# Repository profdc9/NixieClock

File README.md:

This a Nixie clock that uses IN-14 tubes and very generic, cheap, available through-hole parts so that it may be easily sourced in the future.  This material is copyrighted by Daniel Marks (KW4TI) and licensed under the Creative Commons License CC-BY-SA 4.0.  The software is licensed under the zlib license.  These are open source licenses that permit commercial use, modification and redistribution with attribution, and require licensees to assume all risk for using the copyrighted materials.

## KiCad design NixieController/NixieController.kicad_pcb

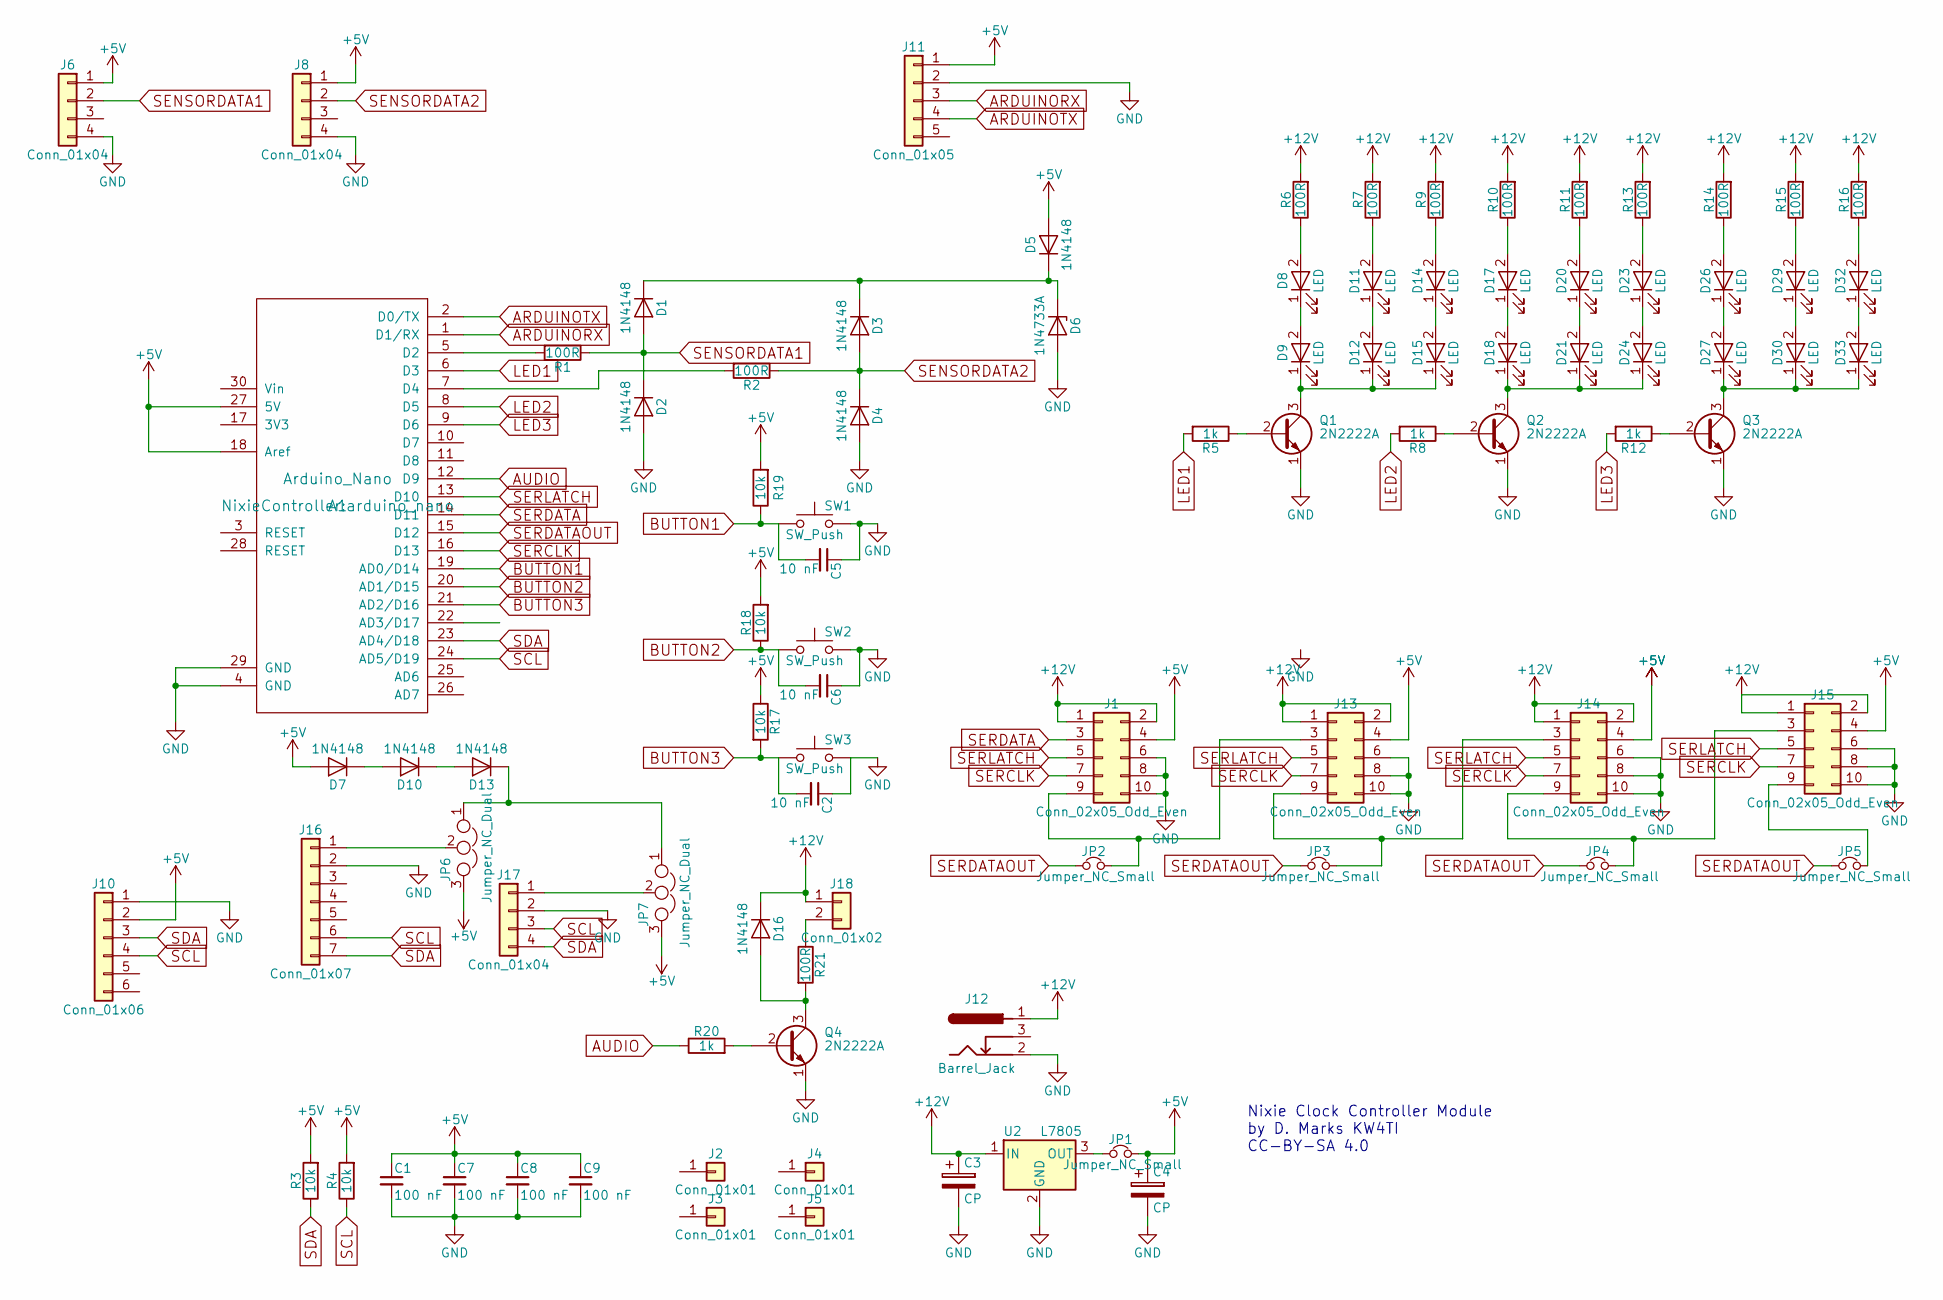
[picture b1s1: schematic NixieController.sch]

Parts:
A1: Arduino_Nano; arduino_nano
C1, C7, C8, C9: 100 nF; C_Disc_D5.0mm_W2.5mm_P2.50mm
C2, C5, C6: 10 nF; C_Disc_D5.0mm_W2.5mm_P2.50mm
C3: CP; CP_Radial_D8.0mm_P3.50mm
C4: CP; CP_Radial_D5.0mm_P2.50mm
D1, D2, D3, D4, D5, D7, D10, D13, D16: 1N4148; D_DO-35_SOD27_P7.62mm_Horizontal
D6: 1N4733A; D_DO-41_SOD81_P7.62mm_Horizontal
D8, D9, D11, D12, D14, D15, D17, D18, D20, D21, D23, D24, D26, D27, D29, D30, D32, D33: LED; LED_D3.0mm
J1, J13, J14, J15: Conn_02x05_Odd_Even; Pin_Header_Straight_2x05_Pitch2.54mm
J2, J3, J4, J5: Conn_01x01; 1pin
J6, J8, J17: Conn_01x04; Pin_Header_Straight_1x04_Pitch2.54mm
J10: Conn_01x06; Pin_Header_Straight_1x06_Pitch2.54mm
J11: Conn_01x05; Pin_Header_Straight_1x05_Pitch2.54mm
J12: Barrel_Jack; BARREL_JACK
J16: Conn_01x07; Pin_Header_Straight_1x07_Pitch2.54mm
J18: Conn_01x02; Molex_KK-6410-02_02x2.54mm_Straight
JP1, JP2, JP3, JP4, JP5: Jumper_NC_Small; Pin_Header_Straight_1x02_Pitch2.54mm
JP6, JP7: Jumper_NC_Dual; Pin_Header_Straight_1x03_Pitch2.54mm
Q1, Q2, Q3, Q4: 2N2222A; TO-92_Molded_Narrow
R1, R2, R6, R7, R9, R10, R11, R13, R14, R15, R16, R21: 100R; R_Axial_DIN0207_L6.3mm_D2.5mm_P7.62mm_Horizontal
R3, R4, R17, R18, R19: 10k; R_Axial_DIN0207_L6.3mm_D2.5mm_P7.62mm_Horizontal
R5, R8, R12, R20: 1k; R_Axial_DIN0207_L6.3mm_D2.5mm_P7.62mm_Horizontal
SW1, SW2, SW3: SW_Push; SW_PUSH_6mm
U2: L7805; TO-220-3_Horizontal

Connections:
+5V: A1.18 (Aref), A1.27 (5V), C1.1, C4.1, C7.1, C8.1, C9.1, D5.2 (A), D7.2 (A), J1.4, J6.1, J8.1, J10.2, J11.1, J13.4, J14.4, J15.4, JP1.2, JP6.3, JP7.3, R3.2, R4.2, R17.1, R18.2, R19.2
+12V: C3.1, D16.1 (K), J1.1, J1.2, J12.1, J13.1, J13.2, J14.1, J14.2, J15.1, J15.2, J18.1, R6.2, R7.2, R9.2, R10.2, R11.2, R13.2, R14.2, R15.2, R16.2, U2.1 (IN)
ARDUINORX: A1.1 (D1/RX), J11.3
ARDUINOTX: A1.2 (D0/TX), J11.4
AUDIO: A1.12 (D9), R20.1
BUTTON1: A1.19 (AD0/D14), C5.2, R19.1, SW1.1
BUTTON2: A1.20 (AD1/D15), C6.2, R18.1, SW2.1
BUTTON3: A1.21 (AD2/D16), C2.2, R17.2, SW3.1
GND: A1.4 (GND), A1.29 (GND), C1.2, C2.1, C3.2, C4.2, C5.1, C6.1, C7.2, C8.2, C9.2, D2.2 (A), D4.2 (A), D6.2 (A), J1.6, J1.8, J1.10, J6.4, J8.4, J10.1, J11.2, J12.2, J13.6, J13.8, J13.10, J14.6, J14.8, J14.10, J15.6, J15.8, J15.10, J16.2, J17.2, Q1.1 (E), Q2.1 (E), Q3.1 (E), Q4.1 (E), SW1.2, SW2.2, SW3.2, U2.2 (GND)
LED1: A1.6 (D3), R5.2
LED2: A1.8 (D5), R8.2
LED3: A1.9 (D6), R12.2
unnamed: A1.5 (D2), R1.2
unnamed: A1.7 (D4), R2.2
unnamed: D1.1 (K), D3.1 (K), D5.1 (K), D6.1 (K)
unnamed: D8.1 (K), D9.2 (A)
unnamed: D8.2 (A), R6.1
unnamed: D10.1 (K), D13.2 (A)
unnamed: D7.1 (K), D10.2 (A)
unnamed: D11.1 (K), D12.2 (A)
unnamed: D11.2 (A), R7.1
unnamed: D9.1 (K), D12.1 (K), D15.1 (K), Q1.3 (C)
unnamed: D13.1 (K), JP6.1, JP7.1
unnamed: D14.1 (K), D15.2 (A)
unnamed: D14.2 (A), R9.1
unnamed: D16.2 (A), Q4.3 (C), R21.2
unnamed: D17.1 (K), D18.2 (A)
unnamed: D17.2 (A), R10.1
unnamed: D18.1 (K), D21.1 (K), D24.1 (K), Q2.3 (C)
unnamed: D20.1 (K), D21.2 (A)
unnamed: D20.2 (A), R11.1
unnamed: D23.1 (K), D24.2 (A)
unnamed: D23.2 (A), R13.1
unnamed: D26.1 (K), D27.2 (A)
unnamed: D26.2 (A), R14.1
unnamed: D27.1 (K), D30.1 (K), D33.1 (K), Q3.3 (C)
unnamed: D29.1 (K), D30.2 (A)
unnamed: D29.2 (A), R15.1
unnamed: D32.1 (K), D33.2 (A)
unnamed: D32.2 (A), R16.1
unnamed: J1.9, J13.3, JP2.2
unnamed: J13.9, J14.3, JP3.2
unnamed: J14.9, J15.3, JP4.2
unnamed: J15.9, JP5.2
unnamed: J16.1, JP6.2
unnamed: J17.1, JP7.2
unnamed: J18.2, R21.1
unnamed: JP1.1, U2.3 (OUT)
unnamed: Q1.2 (B), R5.1
unnamed: Q2.2 (B), R8.1
unnamed: Q3.2 (B), R12.1
unnamed: Q4.2 (B), R20.2
SCL: A1.24 (AD5/D19), J10.4, J16.6, J17.3, R4.1
SDA: A1.23 (AD4/D18), J10.3, J16.7, J17.4, R3.1
SENSORDATA1: D1.2 (A), D2.1 (K), J6.2, R1.1
SENSORDATA2: D3.2 (A), D4.1 (K), J8.2, R2.1
SERCLK: A1.16 (D13), J1.7, J13.7, J14.7, J15.7
SERDATA: A1.14 (D11), J1.3
SERDATAOUT: A1.15 (D12), JP2.1, JP3.1, JP4.1, JP5.1
SERLATCH: A1.13 (D10), J1.5, J13.5, J14.5, J15.5

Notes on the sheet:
Nixie Clock Controller Module by D. Marks KW4TI CC-BY-SA 4.0

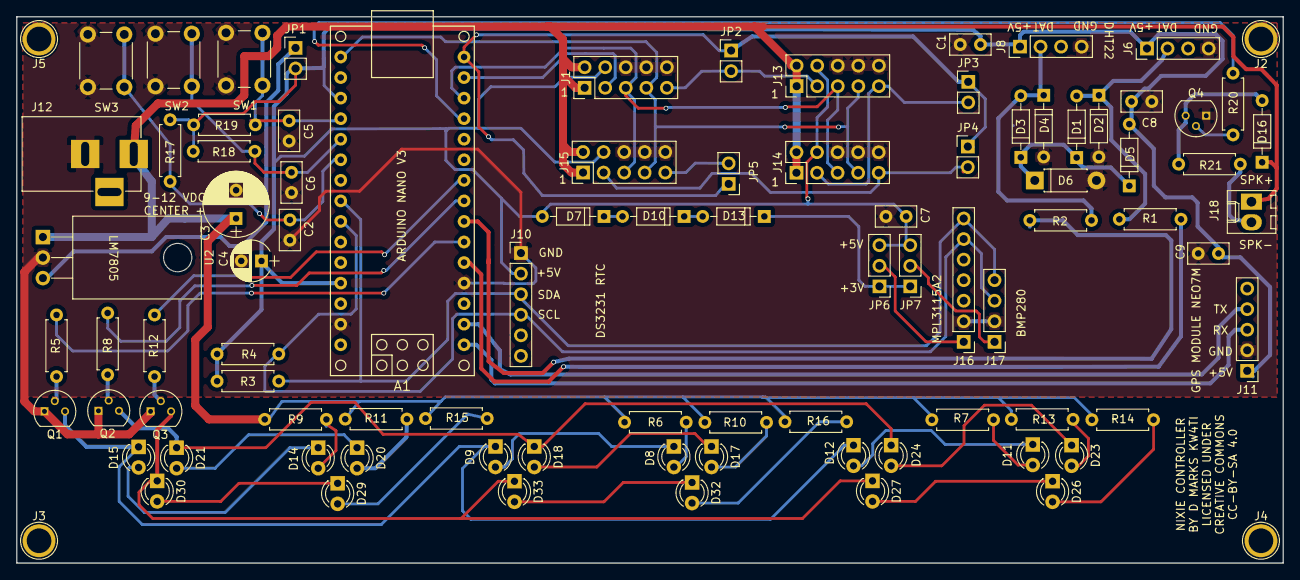
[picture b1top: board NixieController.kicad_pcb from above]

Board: 2 copper layers, 156.5 x 67.5 mm, 90 parts (0 on the bottom side), 60 nets.

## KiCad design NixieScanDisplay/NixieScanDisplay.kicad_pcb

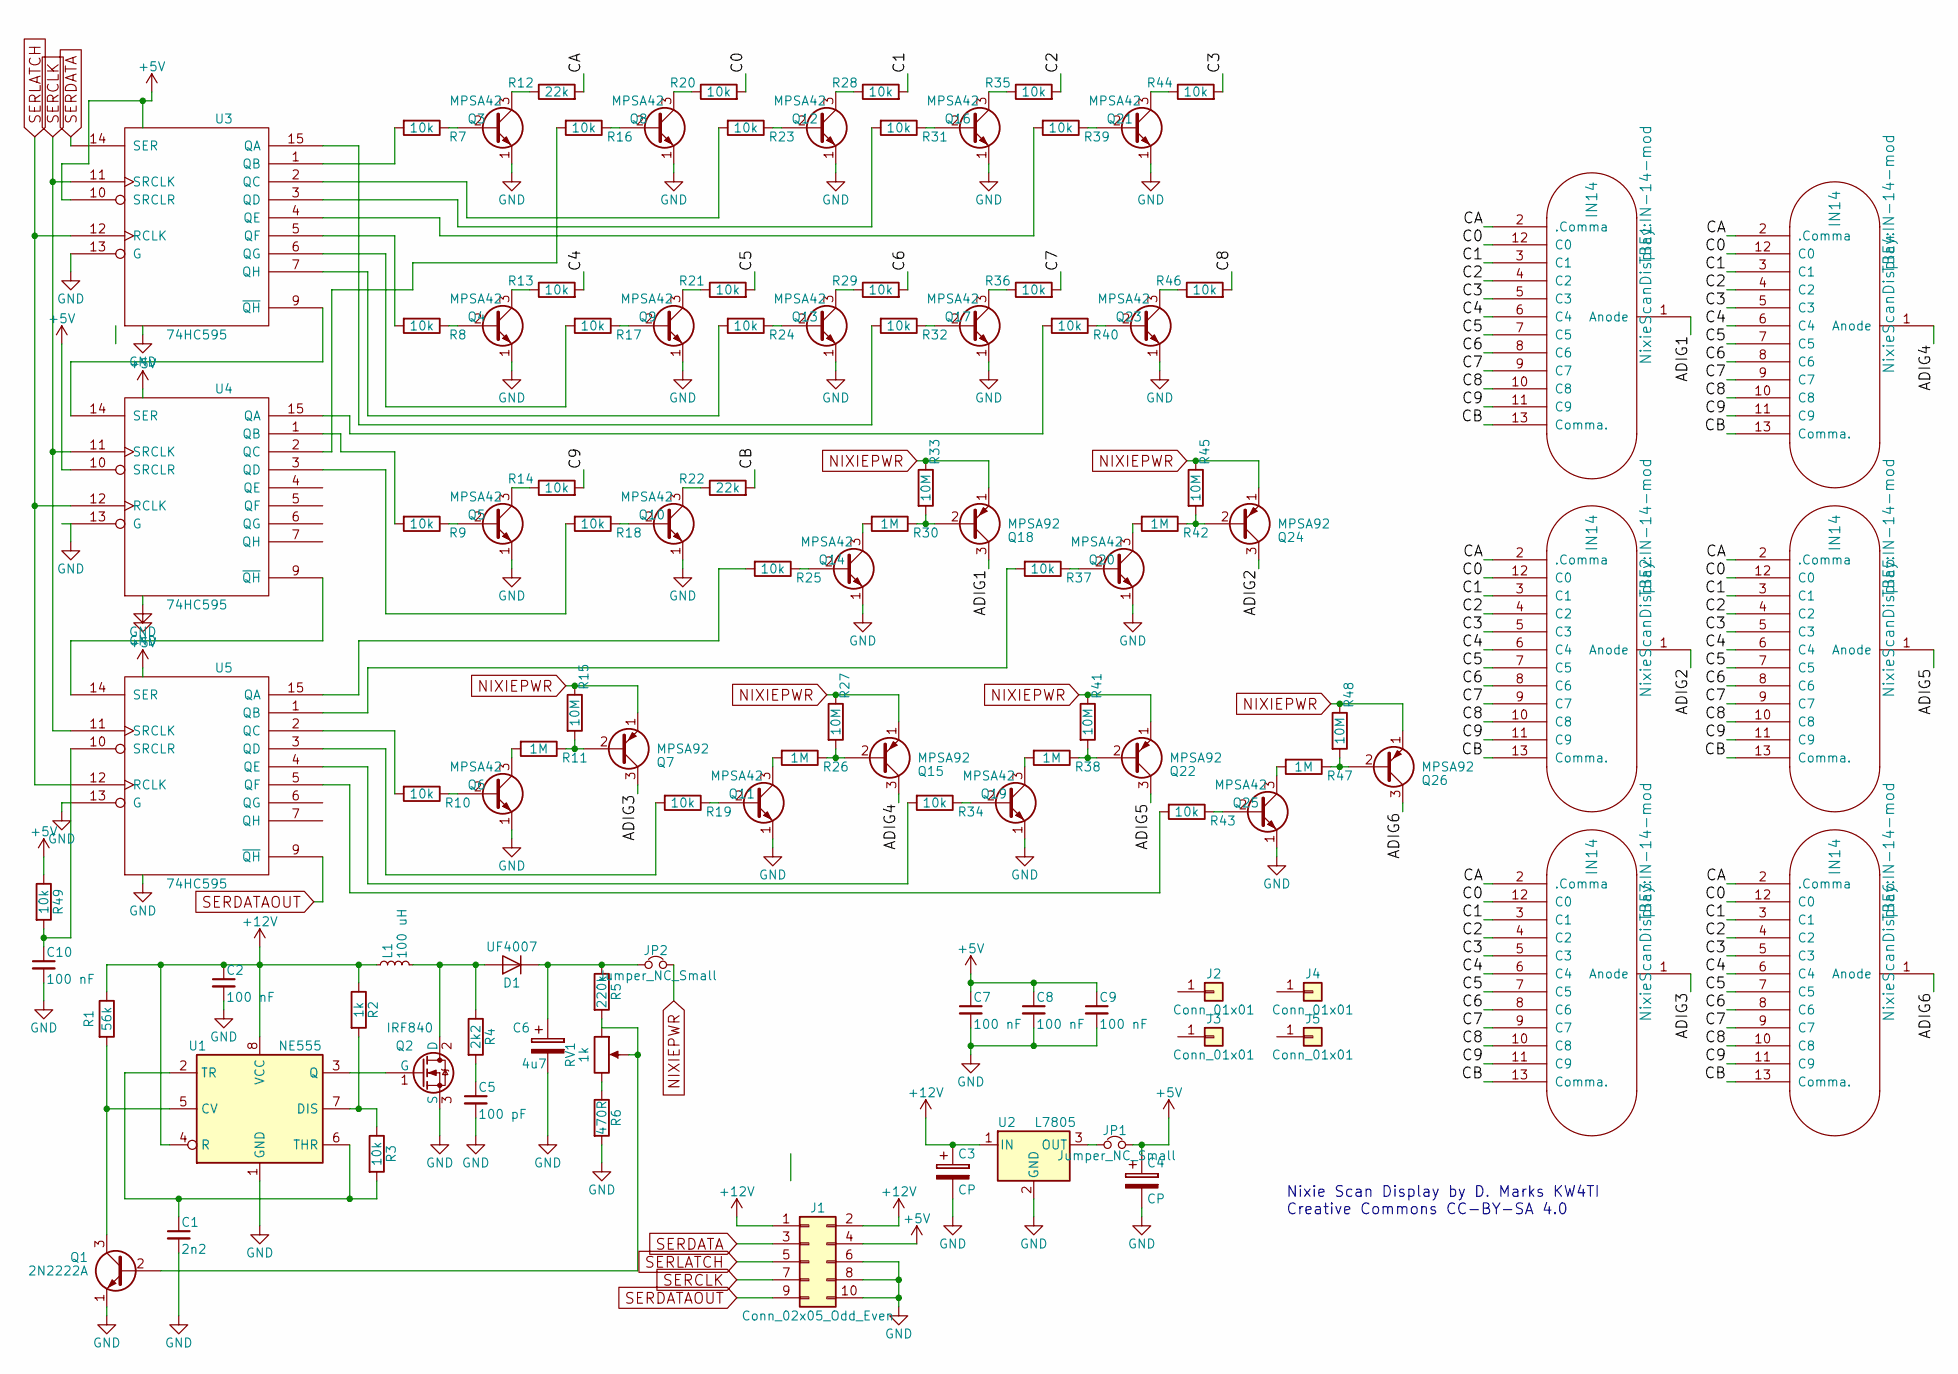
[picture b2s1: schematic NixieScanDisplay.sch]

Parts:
C1: 2n2; C_Disc_D5.0mm_W2.5mm_P2.50mm
C2, C7, C8, C9, C10: 100 nF; C_Disc_D5.0mm_W2.5mm_P2.50mm
C3: CP; CP_Radial_D8.0mm_P3.50mm
C4: CP; CP_Radial_D5.0mm_P2.50mm
C5: 100 pF; C_Disc_D5.0mm_W2.5mm_P2.50mm
C6: 4u7; CP_Radial_D14.0mm_P7.50mm
D1: UF4007; D_DO-41_SOD81_P7.62mm_Horizontal
J1: Conn_02x05_Odd_Even; Pin_Header_Straight_2x05_Pitch2.54mm
J2, J3, J4, J5: Conn_01x01; 1pin
JP1, JP2: Jumper_NC_Small; Pin_Header_Straight_1x02_Pitch2.54mm
L1: 100 uH; L_Toroid_Horizontal_D7.8mm_P13.00mm_Diameter9-5mm_Amidon-T30
Q1: 2N2222A; TO-92_Molded_Narrow
Q2: IRF840; TO-220-3_Vertical
Q3, Q4, Q5, Q6, Q8, Q9, Q10, Q11, Q12, Q13, Q14, Q16, Q17, Q19, Q20, Q21, Q23, Q25: MPSA42; TO-92_Molded_Narrow
Q7, Q15, Q18, Q22, Q24, Q26: MPSA92; TO-92_Molded_Narrow
R1: 56k; R_Axial_DIN0207_L6.3mm_D2.5mm_P7.62mm_Horizontal
R2: 1k; R_Axial_DIN0207_L6.3mm_D2.5mm_P7.62mm_Horizontal
R3, R7, R8, R9, R10, R13, R14, R16, R17, R18, R19, R20, R21, R23, R24, R25, R28, R29, R31, R32, R34, R35, R36, R37, R39, R40, R43, R44, R46, R49: 10k; R_Axial_DIN0207_L6.3mm_D2.5mm_P7.62mm_Horizontal
R4: 2k2; R_Axial_DIN0207_L6.3mm_D2.5mm_P7.62mm_Horizontal
R5: 220k; R_Axial_DIN0207_L6.3mm_D2.5mm_P7.62mm_Horizontal
R6: 470R; R_Axial_DIN0207_L6.3mm_D2.5mm_P7.62mm_Horizontal
R11, R26, R30, R38, R42, R47: 1M; R_Axial_DIN0207_L6.3mm_D2.5mm_P7.62mm_Horizontal
R12, R22: 22k; R_Axial_DIN0207_L6.3mm_D2.5mm_P7.62mm_Horizontal
R15, R27, R33, R41, R45, R48: 10M; R_Axial_DIN0207_L6.3mm_D2.5mm_P7.62mm_Horizontal
RV1: 1k; Potentiometer_Trimmer_Bourns_3296W
TBE1, TBE2, TBE3, TBE4, TBE5, TBE6: IN14; IN-14-mod
U1: NE555; DIP-8_W7.62mm_Socket
U2: L7805; TO-220-3_Vertical
U3, U4, U5: 74HC595; DIP-16_W7.62mm_Socket

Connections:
+5V: C4.1, C7.1, C8.1, C9.1, J1.4, JP1.2, R49.1, U3.10 (SRCLR), U3.16 (VCC), U4.10 (SRCLR), U4.16 (VCC), U5.16 (VCC)
+12V: C2.1, C3.1, J1.1, J1.2, L1.1, R1.1, R2.1, U1.4 (R), U1.8 (VCC), U2.1 (IN)
/ADIG1: Q18.3 (C), TBE1.1 (Anode)
/ADIG2: Q24.3 (C), TBE2.1 (Anode)
/ADIG3: Q7.3 (C), TBE3.1 (Anode)
/ADIG4: Q15.3 (C), TBE4.1 (Anode)
/ADIG5: Q22.3 (C), TBE5.1 (Anode)
/ADIG6: Q26.3 (C), TBE6.1 (Anode)
/C0: R20.2, TBE1.12 (C0), TBE2.12 (C0), TBE3.12 (C0), TBE4.12 (C0), TBE5.12 (C0), TBE6.12 (C0)
/C1: R28.2, TBE1.3 (C1), TBE2.3 (C1), TBE3.3 (C1), TBE4.3 (C1), TBE5.3 (C1), TBE6.3 (C1)
/C2: R35.2, TBE1.4 (C2), TBE2.4 (C2), TBE3.4 (C2), TBE4.4 (C2), TBE5.4 (C2), TBE6.4 (C2)
/C3: R44.2, TBE1.5 (C3), TBE2.5 (C3), TBE3.5 (C3), TBE4.5 (C3), TBE5.5 (C3), TBE6.5 (C3)
/C4: R13.2, TBE1.6 (C4), TBE2.6 (C4), TBE3.6 (C4), TBE4.6 (C4), TBE5.6 (C4), TBE6.6 (C4)
/C5: R21.2, TBE1.7 (C5), TBE2.7 (C5), TBE3.7 (C5), TBE4.7 (C5), TBE5.7 (C5), TBE6.7 (C5)
/C6: R29.2, TBE1.8 (C6), TBE2.8 (C6), TBE3.8 (C6), TBE4.8 (C6), TBE5.8 (C6), TBE6.8 (C6)
/C7: R36.2, TBE1.9 (C7), TBE2.9 (C7), TBE3.9 (C7), TBE4.9 (C7), TBE5.9 (C7), TBE6.9 (C7)
/C8: R46.2, TBE1.10 (C8), TBE2.10 (C8), TBE3.10 (C8), TBE4.10 (C8), TBE5.10 (C8), TBE6.10 (C8)
/C9: R14.2, TBE1.11 (C9), TBE2.11 (C9), TBE3.11 (C9), TBE4.11 (C9), TBE5.11 (C9), TBE6.11 (C9)
/CA: R12.2, TBE1.2 (.Comma), TBE2.2 (.Comma), TBE3.2 (.Comma), TBE4.2 (.Comma), TBE5.2 (.Comma), TBE6.2 (.Comma)
/CB: R22.2, TBE1.13 (Comma.), TBE2.13 (Comma.), TBE3.13 (Comma.), TBE4.13 (Comma.), TBE5.13 (Comma.), TBE6.13 (Comma.)
GND: C1.2, C2.2, C3.2, C4.2, C5.2, C6.2, C7.2, C8.2, C9.2, C10.2, J1.6, J1.8, J1.10, Q1.1 (E), Q2.3 (S), Q3.1 (E), Q4.1 (E), Q5.1 (E), Q6.1 (E), Q8.1 (E), Q9.1 (E), Q10.1 (E), Q11.1 (E), Q12.1 (E), Q13.1 (E), Q14.1 (E), Q16.1 (E), Q17.1 (E), Q19.1 (E), Q20.1 (E), Q21.1 (E), Q23.1 (E), Q25.1 (E), R6.2, U1.1 (GND), U2.2 (GND), U3.8 (GND), U3.13 (G), U4.8 (GND), U4.13 (G), U5.8 (GND), U5.13 (G)
NIXIEPWR: JP2.2, Q7.1 (E), Q15.1 (E), Q18.1 (E), Q22.1 (E), Q24.1 (E), Q26.1 (E), R15.1, R27.1, R33.1, R41.1, R45.1, R48.1
unnamed: C1.1, R3.2, U1.2 (TR), U1.6 (THR)
unnamed: C5.1, R4.2
unnamed: C6.1, D1.1 (K), JP2.1, R5.1
unnamed: C10.1, R49.2, U5.10 (SRCLR)
unnamed: D1.2 (A), L1.2, Q2.2 (D), R4.1
unnamed: JP1.1, U2.3 (OUT)
unnamed: Q1.2 (B), R5.2, RV1.1, RV1.2
unnamed: Q1.3 (C), R1.2, U1.5 (CV)
unnamed: Q2.1 (G), U1.3 (Q)
unnamed: Q3.2 (B), R7.1
unnamed: Q3.3 (C), R12.1
unnamed: Q4.2 (B), R8.1
unnamed: Q4.3 (C), R13.1
unnamed: Q5.2 (B), R9.1
unnamed: Q5.3 (C), R14.1
unnamed: Q6.2 (B), R10.1
unnamed: Q6.3 (C), R11.2
unnamed: Q7.2 (B), R11.1, R15.2
unnamed: Q8.2 (B), R16.1
unnamed: Q8.3 (C), R20.1
unnamed: Q9.2 (B), R17.1
unnamed: Q9.3 (C), R21.1
unnamed: Q10.2 (B), R18.1
unnamed: Q10.3 (C), R22.1
unnamed: Q11.2 (B), R19.1
unnamed: Q11.3 (C), R26.2
unnamed: Q12.2 (B), R23.1
unnamed: Q12.3 (C), R28.1
unnamed: Q13.2 (B), R24.1
unnamed: Q13.3 (C), R29.1
unnamed: Q14.2 (B), R25.1
unnamed: Q14.3 (C), R30.2
unnamed: Q15.2 (B), R26.1, R27.2
unnamed: Q16.2 (B), R31.1
unnamed: Q16.3 (C), R35.1
unnamed: Q17.2 (B), R32.1
unnamed: Q17.3 (C), R36.1
unnamed: Q18.2 (B), R30.1, R33.2
unnamed: Q19.2 (B), R34.1
unnamed: Q19.3 (C), R38.2
unnamed: Q20.2 (B), R37.1
unnamed: Q20.3 (C), R42.2
unnamed: Q21.2 (B), R39.1
unnamed: Q21.3 (C), R44.1
unnamed: Q22.2 (B), R38.1, R41.2
unnamed: Q23.2 (B), R40.1
unnamed: Q23.3 (C), R46.1
unnamed: Q24.2 (B), R42.1, R45.2
unnamed: Q25.2 (B), R43.1
unnamed: Q25.3 (C), R47.2
unnamed: Q26.2 (B), R47.1, R48.2
unnamed: R2.2, R3.1, U1.7 (DIS)
unnamed: R6.1, RV1.3
unnamed: R7.2, U3.1 (QB)
unnamed: R8.2, U3.5 (QF)
unnamed: R9.2, U4.1 (QB)
unnamed: R10.2, U5.2 (QC)
unnamed: R16.2, U4.2 (QC)
unnamed: R17.2, U3.6 (QG)
unnamed: R18.2, U4.3 (QD)
unnamed: R19.2, U5.3 (QD)
unnamed: R23.2, U3.2 (QC)
unnamed: R24.2, U3.7 (QH)
unnamed: R25.2, U5.15 (QA)
unnamed: R31.2, U3.3 (QD)
unnamed: R32.2, U3.15 (QA)
unnamed: R34.2, U5.4 (QE)
unnamed: R37.2, U5.1 (QB)
unnamed: R39.2, U3.4 (QE)
unnamed: R40.2, U4.15 (QA)
unnamed: R43.2, U5.5 (QF)
unnamed: U3.9 (~QH), U4.14 (SER)
unnamed: U4.9 (~QH), U5.14 (SER)
SERCLK: J1.7, U3.11 (SRCLK), U4.11 (SRCLK), U5.11 (SRCLK)
SERDATA: J1.3, U3.14 (SER)
SERDATAOUT: J1.9, U5.9 (~QH)
SERLATCH: J1.5, U3.12 (RCLK), U4.12 (RCLK), U5.12 (RCLK)

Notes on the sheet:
Nixie Scan Display by D. Marks KW4TI Creative Commons CC-BY-SA 4.0

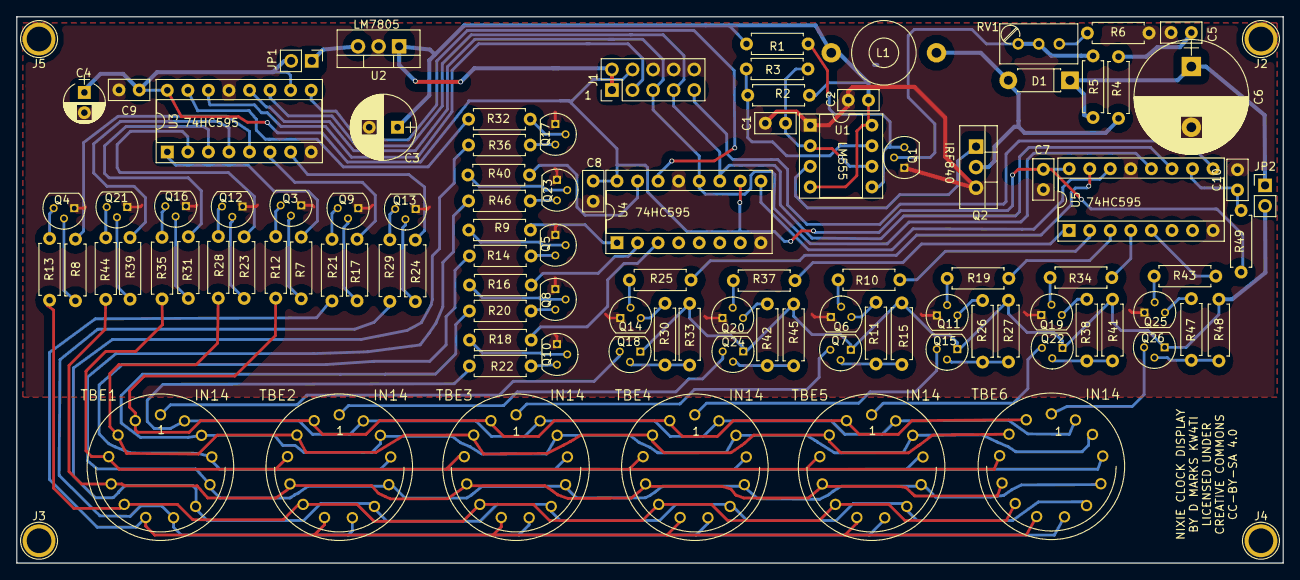
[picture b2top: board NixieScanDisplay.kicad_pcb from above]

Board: 2 copper layers, 156.5 x 67.5 mm, 106 parts (0 on the bottom side), 99 nets.

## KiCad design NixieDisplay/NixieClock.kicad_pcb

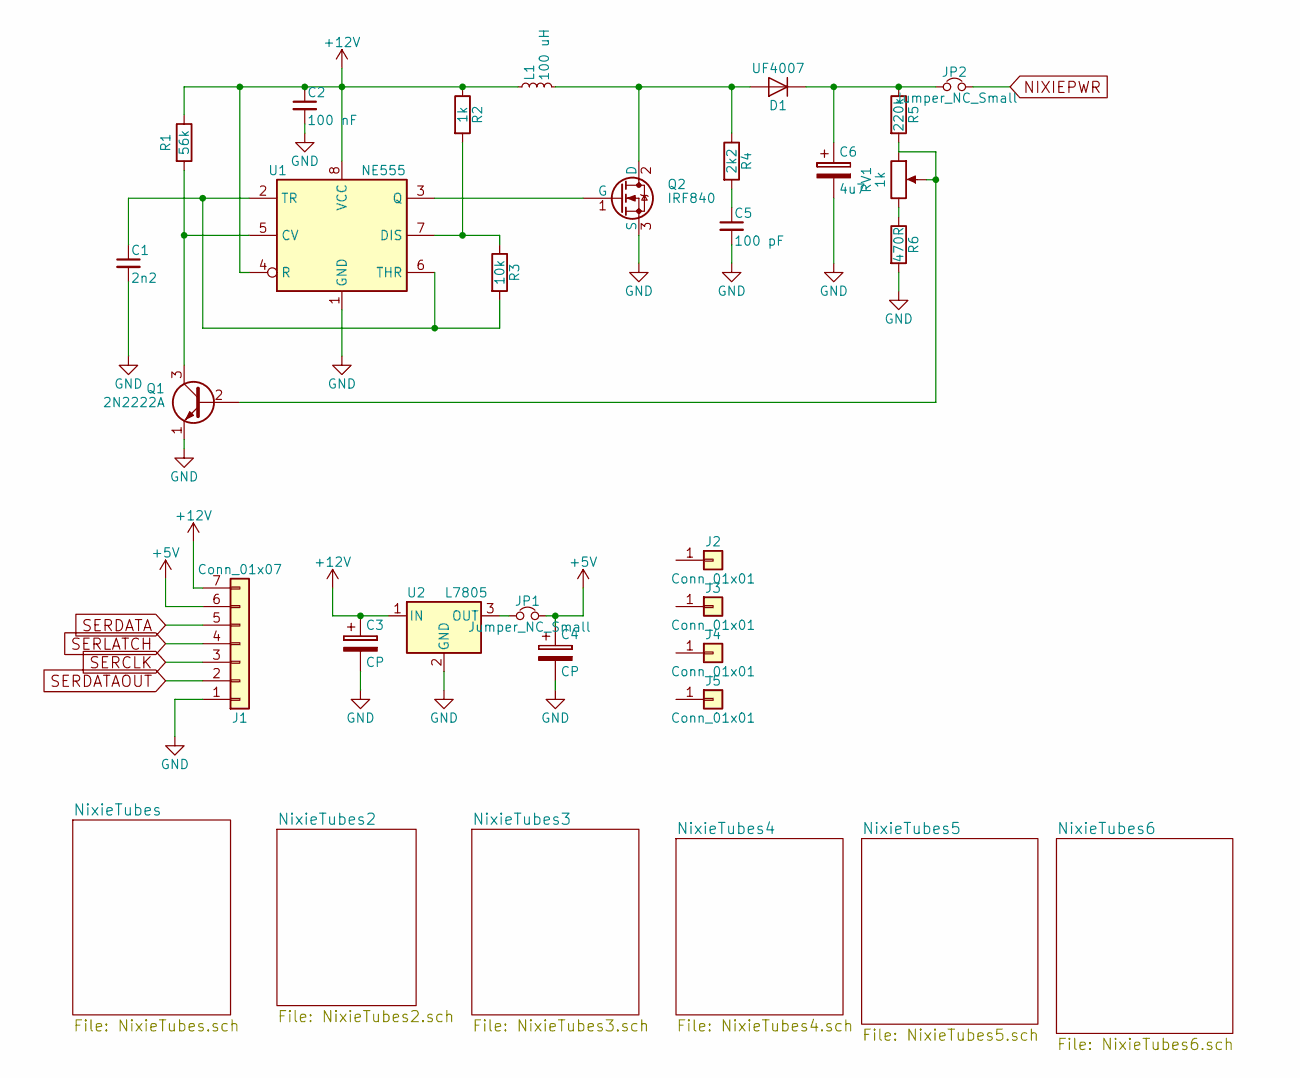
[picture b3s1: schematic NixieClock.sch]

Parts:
C1: 2n2; C_Disc_D5.0mm_W2.5mm_P2.50mm
C2: 100 nF; C_Disc_D5.0mm_W2.5mm_P2.50mm
C3: CP; CP_Radial_D8.0mm_P3.50mm
C4: CP; CP_Radial_D5.0mm_P2.50mm
C5: 100 pF; C_Disc_D5.0mm_W2.5mm_P2.50mm
C6: 4u7; CP_Radial_D8.0mm_P3.50mm
D1: UF4007; D_DO-41_SOD81_P7.62mm_Horizontal
J1: Conn_01x07; Molex_KK-6410-07_07x2.54mm_Straight
J2, J3, J4, J5: Conn_01x01; 1pin
JP1, JP2: Jumper_NC_Small; Pin_Header_Straight_1x02_Pitch2.54mm
L1: 100 uH; L_Toroid_Horizontal_D7.8mm_P13.00mm_Diameter9-5mm_Amidon-T30
Q1: 2N2222A; TO-92_Molded_Narrow
Q2: IRF840; TO-220-3_Vertical
R1: 56k; R_Axial_DIN0207_L6.3mm_D2.5mm_P7.62mm_Horizontal
R2: 1k; R_Axial_DIN0207_L6.3mm_D2.5mm_P7.62mm_Horizontal
R3: 10k; R_Axial_DIN0207_L6.3mm_D2.5mm_P7.62mm_Horizontal
R4: 2k2; R_Axial_DIN0207_L6.3mm_D2.5mm_P7.62mm_Horizontal
R5: 220k; R_Axial_DIN0207_L6.3mm_D2.5mm_P7.62mm_Horizontal
R6: 470R; R_Axial_DIN0207_L6.3mm_D2.5mm_P7.62mm_Horizontal
RV1: 1k; Potentiometer_Trimmer_Bourns_3296W
U1: NE555; DIP-8_W7.62mm_Socket
U2: L7805; TO-220-3_Vertical

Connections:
+5V: C4.1, J1.6, JP1.2; also elsewhere on the board
+12V: C2.1, C3.1, J1.7, L1.1, R1.1, R2.1, U1.4 (R), U1.8 (VCC), U2.1 (IN)
GND: C1.2, C2.2, C3.2, C4.2, C5.2, C6.2, J1.1, Q1.1 (E), Q2.3 (S), R6.2, U1.1 (GND), U2.2 (GND); also elsewhere on the board
NIXIEPWR: JP2.2; also elsewhere on the board
unnamed: C1.1, R3.2, U1.2 (TR), U1.6 (THR)
unnamed: C5.1, R4.2
unnamed: C6.1, D1.1 (K), JP2.1, R5.1
unnamed: D1.2 (A), L1.2, Q2.2 (D), R4.1
unnamed: JP1.1, U2.3 (OUT)
unnamed: Q1.2 (B), R5.2, RV1.1, RV1.2
unnamed: Q1.3 (C), R1.2, U1.5 (CV)
unnamed: Q2.1 (G), U1.3 (Q)
unnamed: R2.2, R3.1, U1.7 (DIS)
unnamed: R6.1, RV1.3
SERCLK: J1.3; also elsewhere on the board
SERDATA: J1.5; also elsewhere on the board
SERDATAOUT: J1.2; also elsewhere on the board
SERLATCH: J1.4; also elsewhere on the board

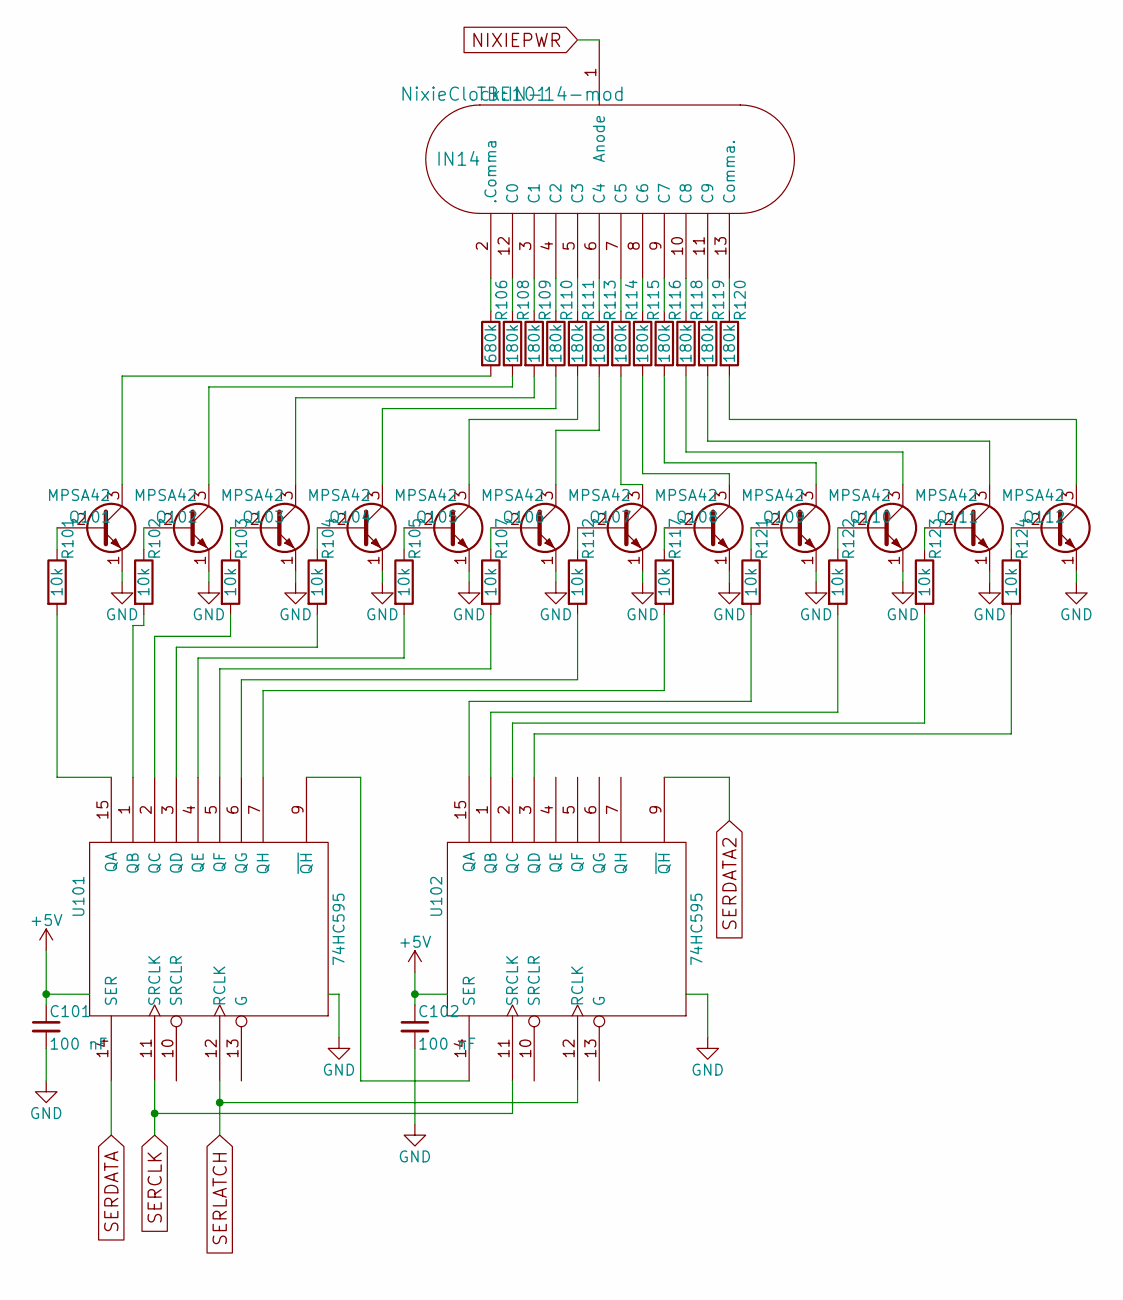
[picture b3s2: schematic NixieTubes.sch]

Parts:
C101, C102: 100 nF; C_Disc_D5.0mm_W2.5mm_P2.50mm
Q101, Q102, Q103, Q104, Q105, Q106, Q107, Q108, Q109, Q110, Q111, Q112: MPSA42; TO-92_Molded_Narrow
R101, R102, R103, R104, R105, R107, R112, R117, R121, R122, R123, R124: 10k; R_Axial_DIN0207_L6.3mm_D2.5mm_P7.62mm_Horizontal
R106: 680k; R_Axial_DIN0207_L6.3mm_D2.5mm_P7.62mm_Horizontal
R108, R109, R110, R111, R113, R114, R115, R116, R118, R119, R120: 180k; R_Axial_DIN0207_L6.3mm_D2.5mm_P7.62mm_Horizontal
TBE101: IN14; IN-14-mod
U101, U102: 74HC595; DIP-16_W7.62mm_Socket

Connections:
+5V: C101.1, C102.1, U101.16 (VCC), U102.16 (VCC); also elsewhere on the board
GND: C101.2, C102.2, Q101.1 (E), Q102.1 (E), Q103.1 (E), Q104.1 (E), Q105.1 (E), Q106.1 (E), Q107.1 (E), Q108.1 (E), Q109.1 (E), Q110.1 (E), Q111.1 (E), Q112.1 (E), U101.8 (GND), U102.8 (GND); also elsewhere on the board
NIXIEPWR: TBE101.1 (Anode); also elsewhere on the board
unnamed: Q101.2 (B), R101.1
unnamed: Q101.3 (C), R106.2
unnamed: Q102.2 (B), R102.1
unnamed: Q102.3 (C), R108.2
unnamed: Q103.2 (B), R103.1
unnamed: Q103.3 (C), R109.2
unnamed: Q104.2 (B), R104.1
unnamed: Q104.3 (C), R110.2
unnamed: Q105.2 (B), R105.1
unnamed: Q105.3 (C), R111.2
unnamed: Q106.2 (B), R107.1
unnamed: Q106.3 (C), R113.2
unnamed: Q107.2 (B), R112.1
unnamed: Q107.3 (C), R114.2
unnamed: Q108.2 (B), R117.1
unnamed: Q108.3 (C), R115.2
unnamed: Q109.2 (B), R121.1
unnamed: Q109.3 (C), R116.2
unnamed: Q110.2 (B), R122.1
unnamed: Q110.3 (C), R118.2
unnamed: Q111.2 (B), R123.1
unnamed: Q111.3 (C), R119.2
unnamed: Q112.2 (B), R124.1
unnamed: Q112.3 (C), R120.2
unnamed: R101.2, U101.15 (QA)
unnamed: R102.2, U101.1 (QB)
unnamed: R103.2, U101.2 (QC)
unnamed: R104.2, U101.3 (QD)
unnamed: R105.2, U101.4 (QE)
unnamed: R106.1, TBE101.2 (.Comma)
unnamed: R107.2, U101.5 (QF)
unnamed: R108.1, TBE101.12 (C0)
unnamed: R109.1, TBE101.3 (C1)
unnamed: R110.1, TBE101.4 (C2)
unnamed: R111.1, TBE101.5 (C3)
unnamed: R112.2, U101.6 (QG)
unnamed: R113.1, TBE101.6 (C4)
unnamed: R114.1, TBE101.7 (C5)
unnamed: R115.1, TBE101.8 (C6)
unnamed: R116.1, TBE101.9 (C7)
unnamed: R117.2, U101.7 (QH)
unnamed: R118.1, TBE101.10 (C8)
unnamed: R119.1, TBE101.11 (C9)
unnamed: R120.1, TBE101.13 (Comma.)
unnamed: R121.2, U102.15 (QA)
unnamed: R122.2, U102.1 (QB)
unnamed: R123.2, U102.2 (QC)
unnamed: R124.2, U102.3 (QD)
unnamed: U101.9 (~QH), U102.14 (SER)
SERCLK: U101.11 (SRCLK), U102.11 (SRCLK); also elsewhere on the board
SERDATA: U101.14 (SER); also elsewhere on the board
SERDATA2: U102.9 (~QH); also elsewhere on the board
SERLATCH: U101.12 (RCLK), U102.12 (RCLK); also elsewhere on the board

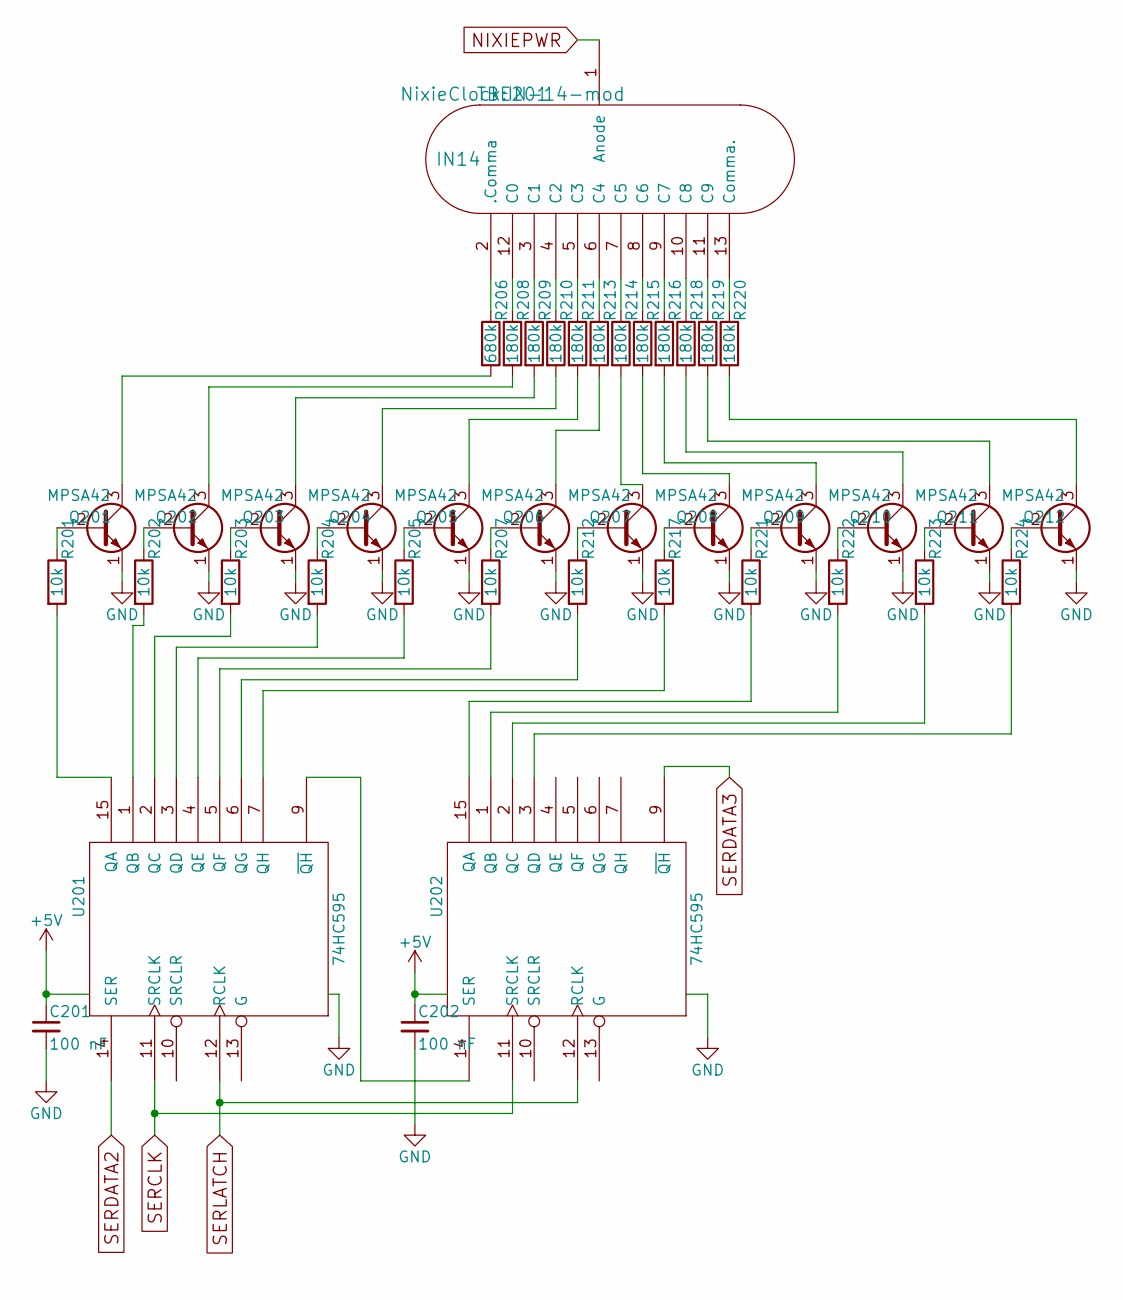
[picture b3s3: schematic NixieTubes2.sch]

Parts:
C201, C202: 100 nF; C_Disc_D5.0mm_W2.5mm_P2.50mm
Q201, Q202, Q203, Q204, Q205, Q206, Q207, Q208, Q209, Q210, Q211, Q212: MPSA42; TO-92_Molded_Narrow
R201, R202, R203, R204, R205, R207, R212, R217, R221, R222, R223, R224: 10k; R_Axial_DIN0207_L6.3mm_D2.5mm_P7.62mm_Horizontal
R206: 680k; R_Axial_DIN0207_L6.3mm_D2.5mm_P7.62mm_Horizontal
R208, R209, R210, R211, R213, R214, R215, R216, R218, R219, R220: 180k; R_Axial_DIN0207_L6.3mm_D2.5mm_P7.62mm_Horizontal
TBE201: IN14; IN-14-mod
U201, U202: 74HC595; DIP-16_W7.62mm_Socket

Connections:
+5V: C201.1, C202.1, U201.16 (VCC), U202.16 (VCC); also elsewhere on the board
GND: C201.2, C202.2, Q201.1 (E), Q202.1 (E), Q203.1 (E), Q204.1 (E), Q205.1 (E), Q206.1 (E), Q207.1 (E), Q208.1 (E), Q209.1 (E), Q210.1 (E), Q211.1 (E), Q212.1 (E), U201.8 (GND), U202.8 (GND); also elsewhere on the board
NIXIEPWR: TBE201.1 (Anode); also elsewhere on the board
unnamed: Q201.2 (B), R201.1
unnamed: Q201.3 (C), R206.2
unnamed: Q202.2 (B), R202.1
unnamed: Q202.3 (C), R208.2
unnamed: Q203.2 (B), R203.1
unnamed: Q203.3 (C), R209.2
unnamed: Q204.2 (B), R204.1
unnamed: Q204.3 (C), R210.2
unnamed: Q205.2 (B), R205.1
unnamed: Q205.3 (C), R211.2
unnamed: Q206.2 (B), R207.1
unnamed: Q206.3 (C), R213.2
unnamed: Q207.2 (B), R212.1
unnamed: Q207.3 (C), R214.2
unnamed: Q208.2 (B), R217.1
unnamed: Q208.3 (C), R215.2
unnamed: Q209.2 (B), R221.1
unnamed: Q209.3 (C), R216.2
unnamed: Q210.2 (B), R222.1
unnamed: Q210.3 (C), R218.2
unnamed: Q211.2 (B), R223.1
unnamed: Q211.3 (C), R219.2
unnamed: Q212.2 (B), R224.1
unnamed: Q212.3 (C), R220.2
unnamed: R201.2, U201.15 (QA)
unnamed: R202.2, U201.1 (QB)
unnamed: R203.2, U201.2 (QC)
unnamed: R204.2, U201.3 (QD)
unnamed: R205.2, U201.4 (QE)
unnamed: R206.1, TBE201.2 (.Comma)
unnamed: R207.2, U201.5 (QF)
unnamed: R208.1, TBE201.12 (C0)
unnamed: R209.1, TBE201.3 (C1)
unnamed: R210.1, TBE201.4 (C2)
unnamed: R211.1, TBE201.5 (C3)
unnamed: R212.2, U201.6 (QG)
unnamed: R213.1, TBE201.6 (C4)
unnamed: R214.1, TBE201.7 (C5)
unnamed: R215.1, TBE201.8 (C6)
unnamed: R216.1, TBE201.9 (C7)
unnamed: R217.2, U201.7 (QH)
unnamed: R218.1, TBE201.10 (C8)
unnamed: R219.1, TBE201.11 (C9)
unnamed: R220.1, TBE201.13 (Comma.)
unnamed: R221.2, U202.15 (QA)
unnamed: R222.2, U202.1 (QB)
unnamed: R223.2, U202.2 (QC)
unnamed: R224.2, U202.3 (QD)
unnamed: U201.9 (~QH), U202.14 (SER)
SERCLK: U201.11 (SRCLK), U202.11 (SRCLK); also elsewhere on the board
SERDATA2: U201.14 (SER); also elsewhere on the board
SERDATA3: U202.9 (~QH); also elsewhere on the board
SERLATCH: U201.12 (RCLK), U202.12 (RCLK); also elsewhere on the board
